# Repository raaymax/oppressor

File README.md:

#  Oppressor - The Feline Discomfort Bot

## Description

Welcome to the Oppressor project, where whimsy meets technology! Oppressor is not your typical robot; it doesn't conquer worlds or perform grand feats. Instead, it specializes in a unique and somewhat tongue-in-cheek mission – making cats feel a little uneasy.

## Project Details

Wireless Control: Oppressor is controlled using WiFi UDP packet transmission, allowing you to manipulate its behavior from the comfort of your laptop or any computer. This wireless control adds an element of surprise and delight to the interaction with your feline friends.

- **Custom PCB**: To bring Oppressor to life, we've designed a custom-made PCB (Printed Circuit Board) to ensure efficient and reliable operation. The PCB is at the heart of this project, facilitating seamless communication between the robot's components.

- **3D Printing Models**: We understand that the Oppressor community might want to explore customization. That's why we've included 3D printing models in the repository. These models can be used to create unique, personalized exteriors for your robot. Let your creativity run wild!

- **Video Stream**: Oppressor provides an immersive experience by offering a video stream feature powered by ESP32-CAM. This allows you to see the world from the robot's perspective, making for an even more engaging and entertaining experience.

- **Python Control Code**: The code for controlling Oppressor is written in Python, making it accessible and easy to modify for those who want to tweak the robot's behavior or add new features. This open-source nature encourages collaboration and innovation within the community.

## Purpose

The Oppressor project is all about adding a touch of whimsy to the world of robotics. It's a light-hearted experiment that explores how technology can interact with our four-legged friends. While Oppressor's name might sound intimidating, rest assured, it's all in good fun. Cats won't be harmed, only a little spooked.

## Parts list

- Seeed Xiao ESP32-S3 Sense 
- ESP32 devkitc?
- DC motors with wheels https://botland.com.pl/silniki-dc-katowe-z-przekladnia/3696-kolo-silnik-65x26mm-5v-z-przekladnia-48-1-5903351248129.html

## Build instructions

1. Order or make PCB based on schematics from `PCB/`
2. Print body on 3d printer `Models/Oppressor_body.stl`
3. Program esp32 with firmware from `Firmware/`
4. For esp32 cam https://github.com/rzeldent/esp32cam-rtsp is used
4. Solder all elements on your PCB
5. Assemble robot

## Video stream

[https://github.com/rzeldent/esp32cam-rtsp/tree/feature/seeed_xiao_esp32s3](https://github.com/rzeldent/esp32cam-rtsp/tree/feature/seeed_xiao_esp32s3)

## Usage

Turn on robot and check using USB serial whats it's IP address (baud: 115200). Connect to robot using `Control/` script and use arrows to control it. 
Have fun and go chasing some cats.

## Contributions

Feel free to contribute to Oppressor by adding new control features, enhancing the video stream, creating new 3D printing models, or optimizing the Python control code. This project is a canvas for creativity, where you can experiment with the boundaries of human-robot and feline-robot interactions.

Remember, Oppressor is a project with a sense of humor, aimed at celebrating the quirky relationship between technology and our feline companions. So, join us in creating an amusing and intriguing experience for cats and their humans!

## MIT License

Copyright (c) 2023 Mateusz Russak

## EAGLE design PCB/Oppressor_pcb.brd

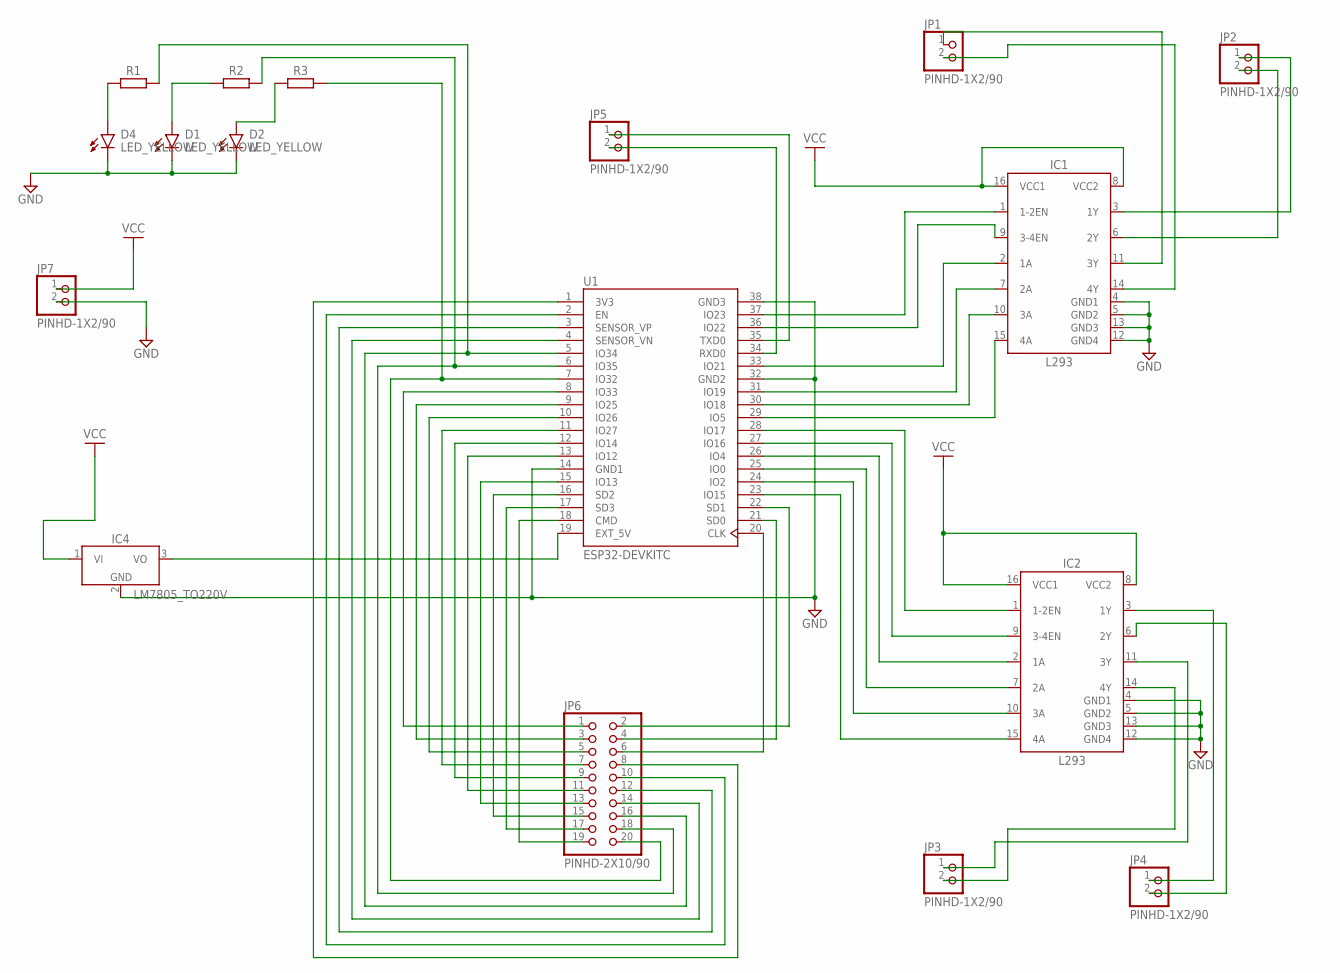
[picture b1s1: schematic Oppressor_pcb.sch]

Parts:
D1, D2, D4: LED_YELLOW; LEDC3224X250N_RND-Y
IC1, IC2: L293; DIP762W53P254L1969H508Q16B
IC4: LM7805_TO220V; TO220V
JP1, JP2, JP3, JP4, JP5, JP7: PINHD-1X2/90; 1X02/90
JP6: PINHD-2X10/90; 2X10/90
R1, R2, R3: R_AXIAL-7.2MM-PITCH; RESAD724W46L381D178B
U1: ESP32-DEVKITC; MODULE_ESP32-DEVKITC

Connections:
GND: D1.C, D2.C, D4.C, IC1.4 (GND1), IC1.5 (GND2), IC1.12 (GND4), IC1.13 (GND3), IC2.4 (GND1), IC2.5 (GND2), IC2.12 (GND4), IC2.13 (GND3), IC4.2 (GND), JP7.2, U1.14 (GND1), U1.32 (GND2), U1.38 (GND3)
unnamed: IC2.3 (1Y), JP4.1
unnamed: IC2.6 (2Y), JP4.2
unnamed: IC2.11 (3Y), JP3.1
unnamed: IC2.14 (4Y), JP3.2
unnamed: IC1.3 (1Y), JP2.1
unnamed: IC1.6 (2Y), JP2.2
unnamed: IC1.11 (3Y), JP1.1
unnamed: IC1.14 (4Y), JP1.2
unnamed: IC4.3 (VO), U1.19 (EXT_5V)
unnamed: IC1.1 (1-2EN), U1.37 (IO23)
unnamed: IC1.9 (3-4EN), U1.36 (IO22)
unnamed: IC1.2 (1A), U1.33 (IO21)
unnamed: IC1.7 (2A), U1.31 (IO19)
unnamed: IC1.10 (3A), U1.30 (IO18)
unnamed: IC1.15 (4A), U1.29 (IO5)
unnamed: IC2.1 (1-2EN), U1.28 (IO17)
unnamed: IC2.9 (3-4EN), U1.27 (IO16)
unnamed: IC2.2 (1A), U1.26 (IO4)
unnamed: IC2.7 (2A), U1.25 (IO0)
unnamed: IC2.10 (3A), U1.24 (IO2)
unnamed: IC2.15 (4A), U1.23 (IO15)
unnamed: JP5.1, U1.35 (TXD0)
unnamed: JP5.2, U1.34 (RXD0)
unnamed: JP6.2, U1.22 (SD1)
unnamed: JP6.4, U1.21 (SD0)
unnamed: JP6.6, U1.20 (CLK)
unnamed: JP6.17, U1.17 (SD3)
unnamed: JP6.19, U1.18 (CMD)
unnamed: JP6.15, U1.16 (SD2)
unnamed: JP6.13, U1.15 (IO13)
unnamed: JP6.11, U1.13 (IO12)
unnamed: JP6.9, U1.12 (IO14)
unnamed: JP6.7, U1.11 (IO27)
unnamed: JP6.5, U1.10 (IO26)
unnamed: JP6.3, U1.9 (IO25)
unnamed: JP6.1, U1.8 (IO33)
unnamed: JP6.14, U1.4 (SENSOR_VN)
unnamed: JP6.12, U1.3 (SENSOR_VP)
unnamed: JP6.10, U1.2 (EN)
unnamed: JP6.8, U1.1 (3V3)
unnamed: D4.A, R1.1
unnamed: D1.A, R2.1
unnamed: D2.A, R3.1
unnamed: JP6.16, R1.2, U1.5 (IO34)
unnamed: JP6.18, R2.2, U1.6 (IO35)
unnamed: JP6.20, R3.2, U1.7 (IO32)
VCC: IC1.8 (VCC2), IC1.16 (VCC1), IC2.8 (VCC2), IC2.16 (VCC1), IC4.1 (VI), JP7.1

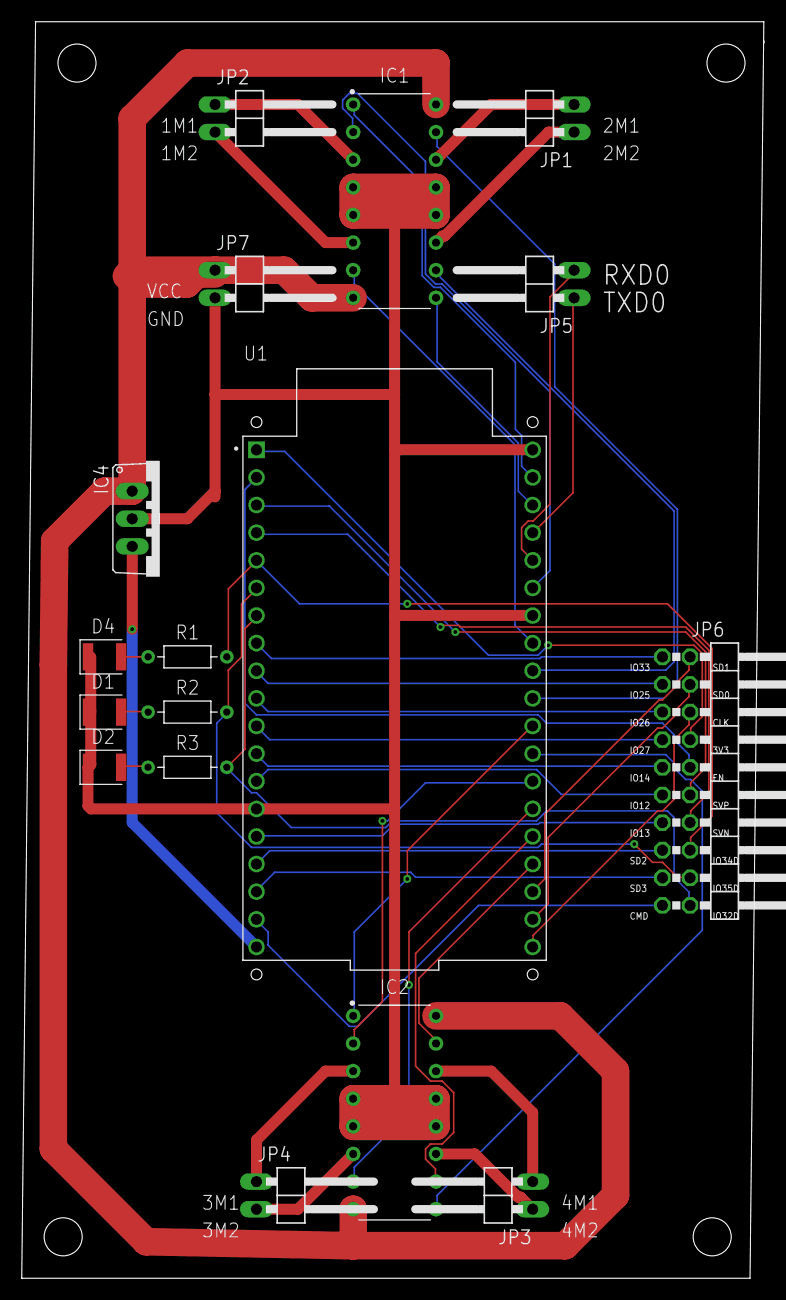
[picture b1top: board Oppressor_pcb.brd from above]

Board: 2 copper layers, 68.2 x 115.4 mm, 17 parts (0 on the bottom side), 48 nets.

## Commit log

2023-11-05 feat: oppressor mk2 robot
